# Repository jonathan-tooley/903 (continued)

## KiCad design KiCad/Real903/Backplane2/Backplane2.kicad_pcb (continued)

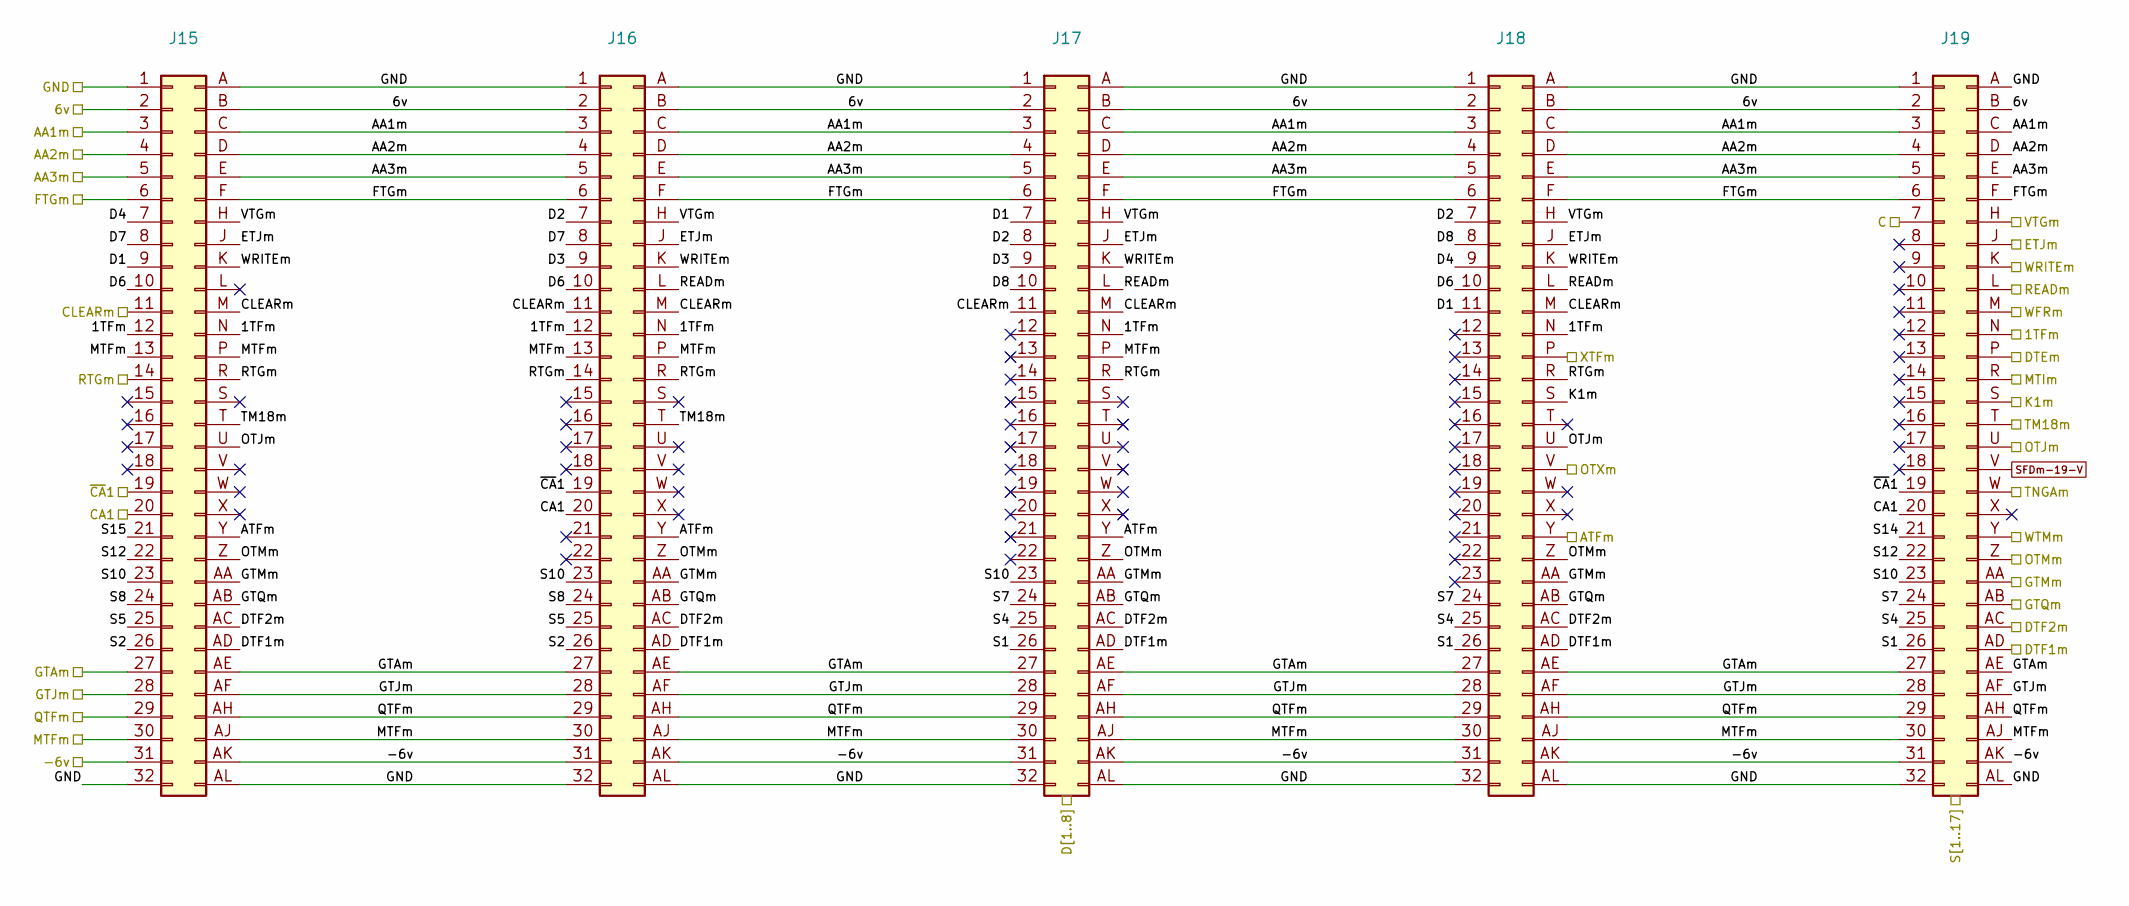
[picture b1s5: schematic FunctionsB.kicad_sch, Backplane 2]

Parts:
J15, J16, J17, J18, J19: DIN41612_B_2x32_Vertical

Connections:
0v: J15.1, J15.32, J15.A, J15.AL, J16.1, J16.32, J16.A, J16.AL, J17.1, J17.32, J17.A, J17.AL, J18.1, J18.32, J18.A, J18.AL, J19.1, J19.32, J19.A, J19.AL; also elsewhere on the board
6v: J15.2, J15.B, J16.2, J16.B, J17.2, J17.B, J18.2, J18.B, J19.2, J19.B; also elsewhere on the board
/DRIVERS/C: J19.7; also elsewhere on the board
/DRIVERS/DTEm: J19.P; also elsewhere on the board
/DRIVERS/MTFm: J15.13, J15.30, J15.AJ, J15.P, J16.13, J16.30, J16.AJ, J16.P, J17.30, J17.AJ, J17.P, J18.30, J18.AJ, J19.30, J19.AJ; also elsewhere on the board
/DRIVERS/MTIm: J19.R; also elsewhere on the board
/DRIVERS/TNGAm: J19.W; also elsewhere on the board
/DRIVERS/WFRm: J19.M; also elsewhere on the board
/DRIVERS/WTMm: J19.Y; also elsewhere on the board
/FunctionsA/1TFm: J15.12, J15.N, J16.12, J16.N, J17.N, J18.N, J19.N; also elsewhere on the board
/FunctionsA/AA1m: J15.3, J15.C, J16.3, J16.C, J17.3, J17.C, J18.3, J18.C, J19.3, J19.C; also elsewhere on the board
/FunctionsA/AA2m: J15.4, J15.D, J16.4, J16.D, J17.4, J17.D, J18.4, J18.D, J19.4, J19.D; also elsewhere on the board
/FunctionsA/AA3m: J15.5, J15.E, J16.5, J16.E, J17.5, J17.E, J18.5, J18.E, J19.5, J19.E; also elsewhere on the board
/FunctionsA/ATFm: J15.Y, J16.Y, J17.Y, J18.Y; also elsewhere on the board
/FunctionsA/D1: J15.9, J17.7, J18.11; also elsewhere on the board
/FunctionsA/D2: J16.7, J17.8, J18.7; also elsewhere on the board
/FunctionsA/D3: J16.9, J17.9; also elsewhere on the board
/FunctionsA/D4: J15.7, J18.9; also elsewhere on the board
/FunctionsA/D6: J15.10, J16.10, J18.10; also elsewhere on the board
/FunctionsA/D7: J15.8, J16.8; also elsewhere on the board
/FunctionsA/D8: J17.10, J18.8; also elsewhere on the board
/FunctionsA/FTGm: J15.6, J15.F, J16.6, J16.F, J17.6, J17.F, J18.6, J18.F, J19.6, J19.F; also elsewhere on the board
/FunctionsA/GTAm: J15.27, J15.AE, J16.27, J16.AE, J17.27, J17.AE, J18.27, J18.AE, J19.27, J19.AE; also elsewhere on the board
/FunctionsA/GTJm: J15.28, J15.AF, J16.28, J16.AF, J17.28, J17.AF, J18.28, J18.AF, J19.28, J19.AF; also elsewhere on the board
/FunctionsA/GTQm: J15.AB, J16.AB, J17.AB, J18.AB, J19.AB; also elsewhere on the board
/FunctionsA/OTJm: J15.U, J18.U, J19.U; also elsewhere on the board
/FunctionsA/OTMm: J15.Z, J16.Z, J17.Z, J18.Z, J19.Z; also elsewhere on the board
/FunctionsA/OTXm: J18.V; also elsewhere on the board
/FunctionsA/READm: J16.L, J17.L, J18.L, J19.L; also elsewhere on the board
/FunctionsA/RTGm: J15.14, J15.R, J16.14, J16.R, J17.R, J18.R; also elsewhere on the board
/FunctionsA/S1: J17.26, J18.26, J19.26; also elsewhere on the board
/FunctionsA/S2: J15.26, J16.26; also elsewhere on the board
/FunctionsA/S4: J17.25, J18.25, J19.25; also elsewhere on the board
/FunctionsA/S5: J15.25, J16.25; also elsewhere on the board
/FunctionsA/S7: J17.24, J18.24, J19.24; also elsewhere on the board
/FunctionsA/S8: J15.24, J16.24; also elsewhere on the board
/FunctionsA/S10: J15.23, J16.23, J17.23, J19.23; also elsewhere on the board
/FunctionsA/S12: J15.22, J19.22; also elsewhere on the board
/FunctionsA/S14: J19.21; also elsewhere on the board
/FunctionsA/S15: J15.21; also elsewhere on the board
/FunctionsA/WRITEm: J15.K, J16.K, J17.K, J18.K, J19.K; also elsewhere on the board
/FunctionsA/XTFm: J18.P; also elsewhere on the board
/FunctionsB/CA1: J15.20, J16.20, J19.20; also elsewhere on the board
/FunctionsB/CLEARm: J15.11, J15.M, J16.11, J16.M, J17.11, J17.M, J18.M; also elsewhere on the board
/FunctionsB/DTF1m: J15.AD, J16.AD, J17.AD, J18.AD, J19.AD; also elsewhere on the board
/FunctionsB/DTF2m: J15.AC, J16.AC, J17.AC, J18.AC, J19.AC; also elsewhere on the board
/FunctionsB/ETJm: J15.J, J16.J, J17.J, J18.J, J19.J; also elsewhere on the board
/FunctionsB/GTMm: J15.AA, J16.AA, J17.AA, J18.AA, J19.AA; also elsewhere on the board
/FunctionsB/K1m: J18.S, J19.S; also elsewhere on the board
/FunctionsB/QTFm: J15.29, J15.AH, J16.29, J16.AH, J17.29, J17.AH, J18.29, J18.AH, J19.29, J19.AH; also elsewhere on the board
/FunctionsB/TM18m: J15.T, J16.T, J19.T; also elsewhere on the board
/FunctionsB/VTGm: J15.H, J16.H, J17.H, J18.H, J19.H; also elsewhere on the board
/FunctionsB/~CA1: J15.19, J16.19, J19.19; also elsewhere on the board
Neg6v: J15.31, J15.AK, J16.31, J16.AK, J17.31, J17.AK, J18.31, J18.AK, J19.31, J19.AK; also elsewhere on the board
SFDm-19-V: J19.V; also elsewhere on the board

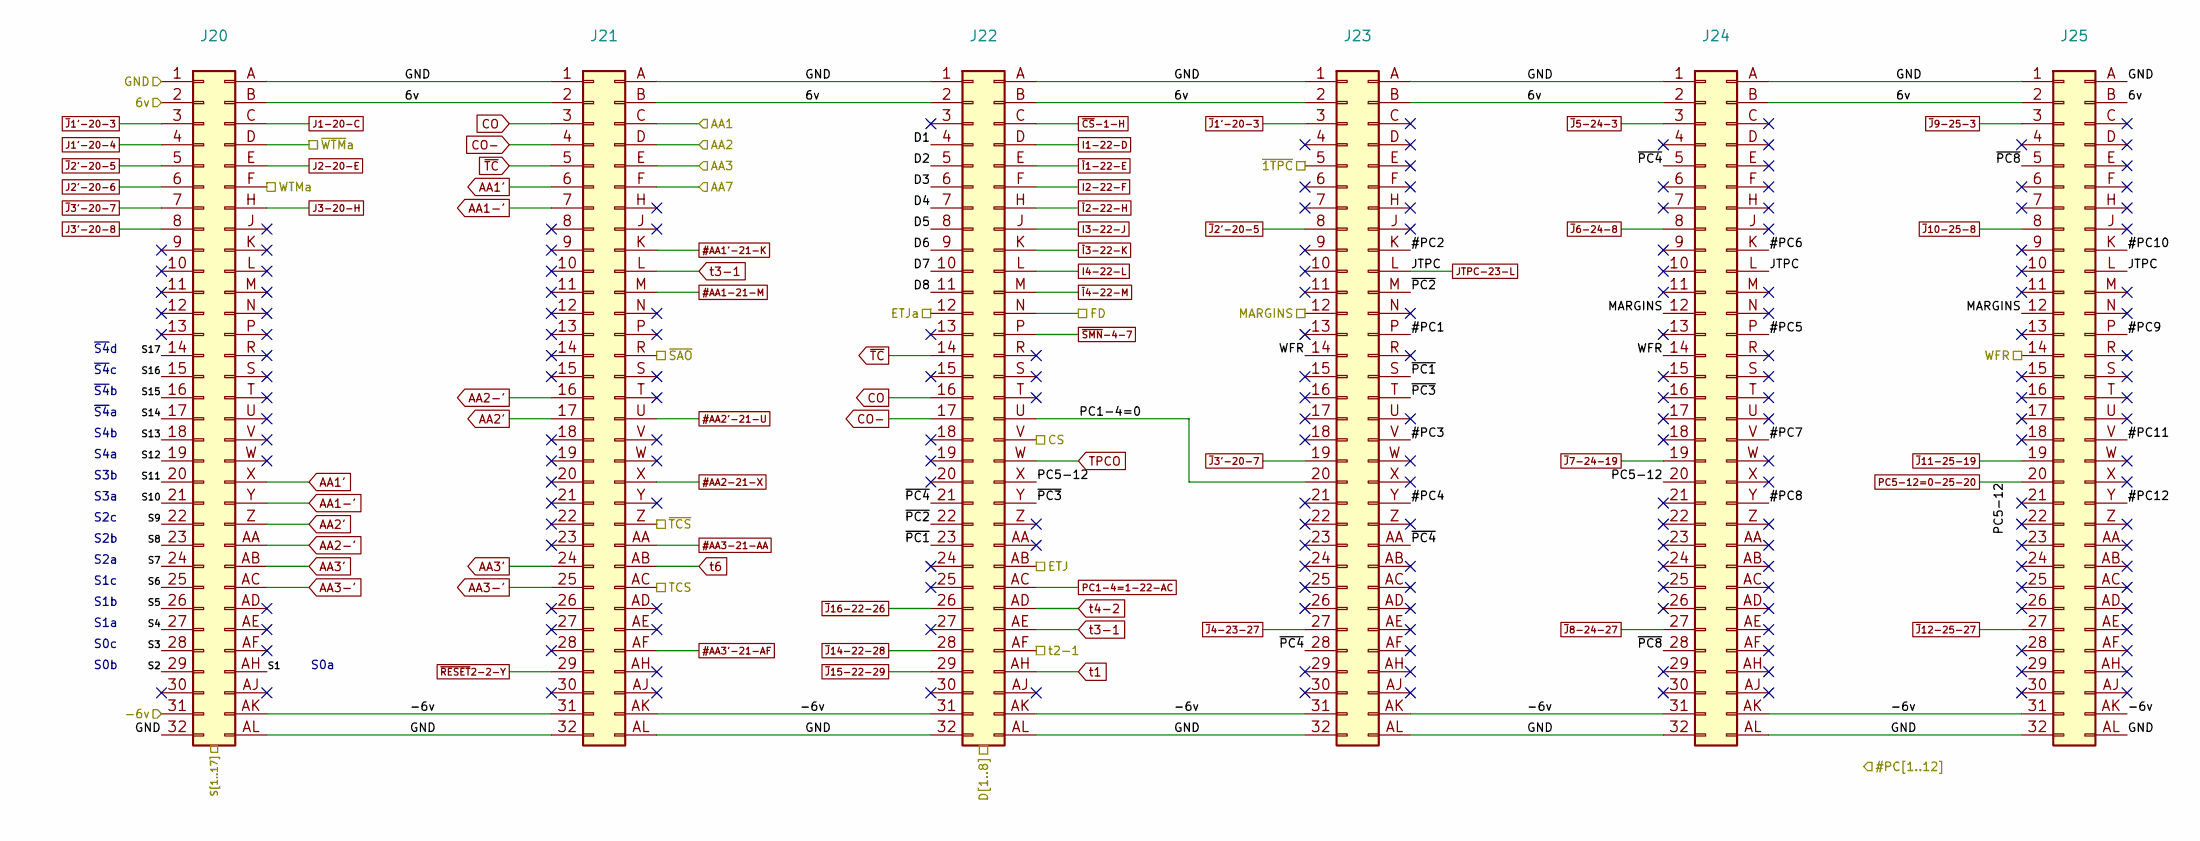
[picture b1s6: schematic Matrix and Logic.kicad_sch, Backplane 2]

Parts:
J20, J21, J22, J23, J24, J25: DIN41612_B_2x32_Vertical

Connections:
0v: J20.1, J20.32, J20.A, J20.AL, J21.1, J21.32, J21.A, J21.AL, J22.1, J22.32, J22.A, J22.AL, J23.1, J23.32, J23.A, J23.AL, J24.1, J24.32, J24.A, J24.AL, J25.1, J25.32, J25.A, J25.AL; also elsewhere on the board
6v: J20.2, J20.B, J21.2, J21.B, J22.2, J22.B, J23.2, J23.B, J24.2, J24.B, J25.2, J25.B; also elsewhere on the board
#AA1'-21-K: J21.K; also elsewhere on the board
#AA1-21-M: J21.M; also elsewhere on the board
#AA2'-21-U: J21.U; also elsewhere on the board
#AA2-21-X: J21.X; also elsewhere on the board
#AA3'-21-AF: J21.AF; also elsewhere on the board
#AA3-21-AA: J21.AA; also elsewhere on the board
/Connections/#PC1: J23.P; also elsewhere on the board
/Connections/#PC2: J23.K; also elsewhere on the board
/Connections/#PC3: J23.V; also elsewhere on the board
/Connections/#PC4: J23.Y; also elsewhere on the board
/Connections/#PC5: J24.P; also elsewhere on the board
/Connections/#PC6: J24.K; also elsewhere on the board
/Connections/#PC7: J24.V; also elsewhere on the board
/Connections/#PC8: J24.Y; also elsewhere on the board
/Connections/#PC9: J25.P; also elsewhere on the board
/Connections/#PC10: J25.K; also elsewhere on the board
/Connections/#PC11: J25.V; also elsewhere on the board
/Connections/#PC12: J25.Y; also elsewhere on the board
/DRIVERS/AA7: J21.F; also elsewhere on the board
/DRIVERS/ETJ: J22.AB; also elsewhere on the board
/DRIVERS/ETJa: J22.12; also elsewhere on the board
/DRIVERS/FD: J22.N; also elsewhere on the board
/DRIVERS/TCS: J21.AC; also elsewhere on the board
/DRIVERS/t2-1: J22.AF; also elsewhere on the board
/DRIVERS/~TCS: J21.Z; also elsewhere on the board
/FunctionsA/AA1m: J21.C; also elsewhere on the board
/FunctionsA/AA2m: J21.D; also elsewhere on the board
/FunctionsA/AA3m: J21.E; also elsewhere on the board
/FunctionsA/D1: J22.4; also elsewhere on the board
/FunctionsA/D2: J22.5; also elsewhere on the board
/FunctionsA/D3: J22.6; also elsewhere on the board
/FunctionsA/D4: J22.7; also elsewhere on the board
/FunctionsA/D5: J22.8; also elsewhere on the board
/FunctionsA/D6: J22.9; also elsewhere on the board
/FunctionsA/D7: J22.10; also elsewhere on the board
/FunctionsA/D8: J22.11; also elsewhere on the board
/FunctionsA/S1: J20.AH; also elsewhere on the board
/FunctionsA/S2: J20.29; also elsewhere on the board
/FunctionsA/S3: J20.28; also elsewhere on the board
/FunctionsA/S4: J20.27; also elsewhere on the board
/FunctionsA/S5: J20.26; also elsewhere on the board
/FunctionsA/S6: J20.25; also elsewhere on the board
/FunctionsA/S7: J20.24; also elsewhere on the board
/FunctionsA/S8: J20.23; also elsewhere on the board
/FunctionsA/S9: J20.22; also elsewhere on the board
/FunctionsA/S10: J20.21; also elsewhere on the board
/FunctionsA/S11: J20.20; also elsewhere on the board
/FunctionsA/S12: J20.19; also elsewhere on the board
/FunctionsA/S13: J20.18; also elsewhere on the board
/FunctionsA/S14: J20.17; also elsewhere on the board
/FunctionsA/S15: J20.16; also elsewhere on the board
/FunctionsA/S16: J20.15; also elsewhere on the board
/FunctionsA/S17: J20.14; also elsewhere on the board
/Matrix and Logic/MARGINS: J23.12, J24.12, J25.12; also elsewhere on the board
/Matrix and Logic/PC1-4=0: J22.U, J23.20
/Matrix and Logic/WFR: J23.14, J24.14, J25.14; also elsewhere on the board
/Matrix and Logic/~1TPC: J23.5; also elsewhere on the board
/Matrix and Logic/~PC1: J22.23, J23.S
/Matrix and Logic/~PC2: J22.22, J23.M
/Matrix and Logic/~PC3: J22.Y, J23.T
/Matrix and Logic/~PC4: J22.21, J23.28, J23.AA, J24.5
/Matrix and Logic/~PC8: J24.28, J25.5
/Matrix and Logic/~WTMa: J20.D; also elsewhere on the board
/TIMING/CS: J22.V; also elsewhere on the board
/TIMING/~SAO: J21.R; also elsewhere on the board
AA1': J20.X, J21.6
AA1-': J20.Y, J21.7
AA2': J20.Z, J21.17
AA2-': J20.AA, J21.16
AA3': J20.AB, J21.24
AA3-': J20.AC, J21.25
CO: J21.3, J22.16
CO-: J21.4, J22.17
I1-22-D: J22.D; also elsewhere on the board
I2-22-F: J22.F; also elsewhere on the board
I3-22-J: J22.J; also elsewhere on the board
I4-22-L: J22.L; also elsewhere on the board
J1'-20-4: J20.4; also elsewhere on the board
J1-20-C: J20.C; also elsewhere on the board
J2'-20-6: J20.6; also elsewhere on the board
J2-20-E: J20.E; also elsewhere on the board
J3'-20-8: J20.8; also elsewhere on the board
J3-20-H: J20.H; also elsewhere on the board
JTPC-23-L: J23.L, J24.L, J25.L; also elsewhere on the board
Neg6v: J20.31, J20.AK, J21.31, J21.AK, J22.31, J22.AK, J23.31, J23.AK, J24.31, J24.AK, J25.31, J25.AK; also elsewhere on the board
PC1-4=1-22-AC: J22.AC; also elsewhere on the board
PC5-12=0-25-20: J22.X, J24.20, J25.20; also elsewhere on the board
TPCO: J22.W; also elsewhere on the board
WTMa-8-21: J20.F; also elsewhere on the board
t1: J22.AH; also elsewhere on the board
t3-1: J21.L, J22.AE
t4-2: J22.AD; also elsewhere on the board
t6: J21.AB; also elsewhere on the board
~CS-1-H: J22.C; also elsewhere on the board
~I1-22-E: J22.E; also elsewhere on the board
~I2-22-H: J22.H; also elsewhere on the board
~I3-22-K: J22.K; also elsewhere on the board
~I4-22-M: J22.M; also elsewhere on the board
~J1'-20-3: J20.3, J23.3; also elsewhere on the board
~J2'-20-5: J20.5, J23.8; also elsewhere on the board
~J3'-20-7: J20.7, J23.19; also elsewhere on the board
~J4-23-27: J23.27; also elsewhere on the board
~J5-24-3: J24.3; also elsewhere on the board
~J6-24-8: J24.8; also elsewhere on the board
~J7-24-19: J24.19; also elsewhere on the board
~J8-24-27: J24.27; also elsewhere on the board
~J9-25-3: J25.3; also elsewhere on the board
~J10-25-8: J25.8; also elsewhere on the board
~J11-25-19: J25.19; also elsewhere on the board
~J12-25-27: J25.27; also elsewhere on the board
~J14-22-28: J22.28; also elsewhere on the board
~J15-22-29: J22.29; also elsewhere on the board
~J16-22-26: J22.26; also elsewhere on the board
~RESET2-2-Y: J21.29; also elsewhere on the board
~SMN-4-7: J22.P; also elsewhere on the board
~TC: J21.5, J22.14

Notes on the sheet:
S1b
S2a
~{S4}b
S0c
S3b
~{S4}a
S2b
~{S4}c
S4b
~{S4}d
S0a
S4a
S1a
S2c
S1c
S0b
S3a

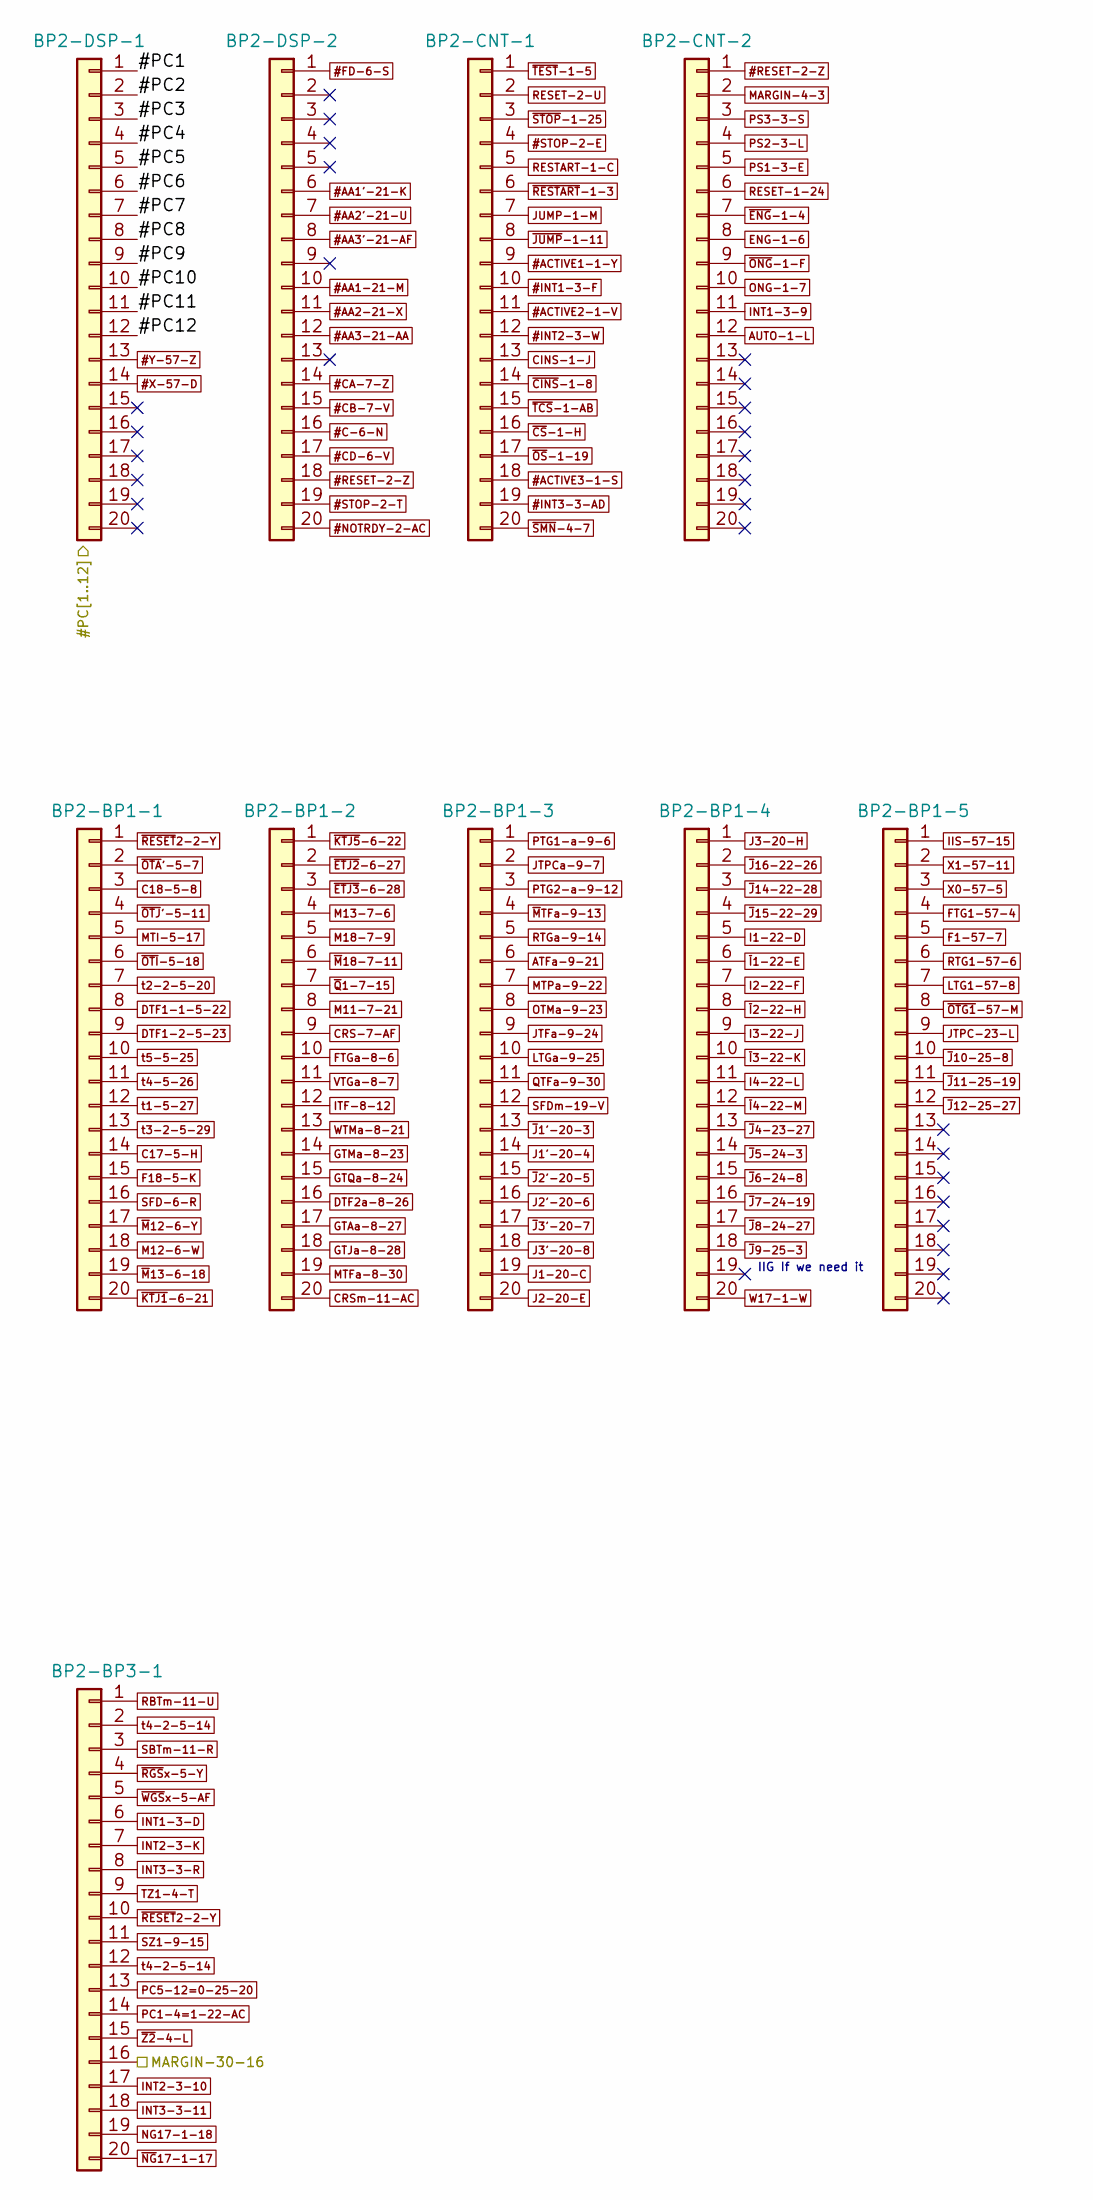
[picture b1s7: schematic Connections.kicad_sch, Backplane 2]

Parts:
BP2-BP1-1, BP2-BP1-2, BP2-BP1-3, BP2-BP1-4, BP2-BP1-5, BP2-BP3-1, BP2-CNT-1, BP2-CNT-2, BP2-DSP-1, BP2-DSP-2: IDC-Header_2x10_P2.54mm_Latch_Vertical

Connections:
#AA1'-21-K: BP2-DSP-2.6; also elsewhere on the board
#AA1-21-M: BP2-DSP-2.10; also elsewhere on the board
#AA2'-21-U: BP2-DSP-2.7; also elsewhere on the board
#AA2-21-X: BP2-DSP-2.11; also elsewhere on the board
#AA3'-21-AF: BP2-DSP-2.8; also elsewhere on the board
#AA3-21-AA: BP2-DSP-2.12; also elsewhere on the board
#ACTIVE1-1-Y: BP2-CNT-1.9; also elsewhere on the board
#ACTIVE2-1-V: BP2-CNT-1.11; also elsewhere on the board
#ACTIVE3-1-S: BP2-CNT-1.18; also elsewhere on the board
#C-6-N: BP2-DSP-2.16; also elsewhere on the board
#CA-7-Z: BP2-DSP-2.14; also elsewhere on the board
#CB-7-V: BP2-DSP-2.15; also elsewhere on the board
#CD-6-V: BP2-DSP-2.17; also elsewhere on the board
#FD-6-S: BP2-DSP-2.1; also elsewhere on the board
#INT1-3-F: BP2-CNT-1.10; also elsewhere on the board
#INT2-3-W: BP2-CNT-1.12; also elsewhere on the board
#INT3-3-AD: BP2-CNT-1.19; also elsewhere on the board
#NOTRDY-2-AC: BP2-DSP-2.20; also elsewhere on the board
#RESET-2-Z: BP2-CNT-2.1, BP2-DSP-2.18; also elsewhere on the board
#STOP-2-E: BP2-CNT-1.4; also elsewhere on the board
#STOP-2-T: BP2-DSP-2.19; also elsewhere on the board
#X-57-D: BP2-DSP-1.14; also elsewhere on the board
#Y-57-Z: BP2-DSP-1.13; also elsewhere on the board
/Connections/#PC1: BP2-DSP-1.1; also elsewhere on the board
/Connections/#PC2: BP2-DSP-1.2; also elsewhere on the board
/Connections/#PC3: BP2-DSP-1.3; also elsewhere on the board
/Connections/#PC4: BP2-DSP-1.4; also elsewhere on the board
/Connections/#PC5: BP2-DSP-1.5; also elsewhere on the board
/Connections/#PC6: BP2-DSP-1.6; also elsewhere on the board
/Connections/#PC7: BP2-DSP-1.7; also elsewhere on the board
/Connections/#PC8: BP2-DSP-1.8; also elsewhere on the board
/Connections/#PC9: BP2-DSP-1.9; also elsewhere on the board
/Connections/#PC10: BP2-DSP-1.10; also elsewhere on the board
/Connections/#PC11: BP2-DSP-1.11; also elsewhere on the board
/Connections/#PC12: BP2-DSP-1.12; also elsewhere on the board
/Matrix and Logic/MARGINS: BP2-BP3-1.16; also elsewhere on the board
ATFa-9-21: BP2-BP1-3.6; also elsewhere on the board
AUTO-1-L: BP2-CNT-2.12; also elsewhere on the board
C17-5-H: BP2-BP1-1.14; also elsewhere on the board
C18-5-8: BP2-BP1-1.3; also elsewhere on the board
CINS-1-J: BP2-CNT-1.13; also elsewhere on the board
CRS-7-AF: BP2-BP1-2.9; also elsewhere on the board
CRSm-11-AC: BP2-BP1-2.20; also elsewhere on the board
DTF1-1-5-22: BP2-BP1-1.8; also elsewhere on the board
DTF1-2-5-23: BP2-BP1-1.9; also elsewhere on the board
DTF2a-8-26: BP2-BP1-2.16; also elsewhere on the board
ENG-1-6: BP2-CNT-2.8; also elsewhere on the board
F1-57-7: BP2-BP1-5.5; also elsewhere on the board
F18-5-K: BP2-BP1-1.15; also elsewhere on the board
FTG1-57-4: BP2-BP1-5.4; also elsewhere on the board
FTGa-8-6: BP2-BP1-2.10; also elsewhere on the board
GTAa-8-27: BP2-BP1-2.17; also elsewhere on the board
GTJa-8-28: BP2-BP1-2.18; also elsewhere on the board
GTMa-8-23: BP2-BP1-2.14; also elsewhere on the board
GTQa-8-24: BP2-BP1-2.15; also elsewhere on the board
I1-22-D: BP2-BP1-4.5; also elsewhere on the board
I2-22-F: BP2-BP1-4.7; also elsewhere on the board
I3-22-J: BP2-BP1-4.9; also elsewhere on the board
I4-22-L: BP2-BP1-4.11; also elsewhere on the board
IIS-57-15: BP2-BP1-5.1; also elsewhere on the board
INT1-3-9: BP2-CNT-2.11; also elsewhere on the board
INT1-3-D: BP2-BP3-1.6; also elsewhere on the board
INT2-3-10: BP2-BP3-1.17; also elsewhere on the board
INT2-3-K: BP2-BP3-1.7; also elsewhere on the board
INT3-3-11: BP2-BP3-1.18; also elsewhere on the board
INT3-3-R: BP2-BP3-1.8; also elsewhere on the board
ITF-8-12: BP2-BP1-2.12; also elsewhere on the board
J1'-20-4: BP2-BP1-3.14; also elsewhere on the board
J1-20-C: BP2-BP1-3.19; also elsewhere on the board
J2'-20-6: BP2-BP1-3.16; also elsewhere on the board
J2-20-E: BP2-BP1-3.20; also elsewhere on the board
J3'-20-8: BP2-BP1-3.18; also elsewhere on the board
J3-20-H: BP2-BP1-4.1; also elsewhere on the board
JTFa-9-24: BP2-BP1-3.9; also elsewhere on the board
JTPC-23-L: BP2-BP1-5.9; also elsewhere on the board
JTPCa-9-7: BP2-BP1-3.2; also elsewhere on the board
JUMP-1-M: BP2-CNT-1.7; also elsewhere on the board
LTG1-57-8: BP2-BP1-5.7; also elsewhere on the board
LTGa-9-25: BP2-BP1-3.10; also elsewhere on the board
M11-7-21: BP2-BP1-2.8; also elsewhere on the board
M12-6-W: BP2-BP1-1.18; also elsewhere on the board
M13-7-6: BP2-BP1-2.4; also elsewhere on the board
M18-7-9: BP2-BP1-2.5; also elsewhere on the board
MARGIN-4-3: BP2-CNT-2.2; also elsewhere on the board
MTFa-8-30: BP2-BP1-2.19; also elsewhere on the board
MTI-5-17: BP2-BP1-1.5; also elsewhere on the board
MTPa-9-22: BP2-BP1-3.7; also elsewhere on the board
NG17-1-18: BP2-BP3-1.19; also elsewhere on the board
ONG-1-7: BP2-CNT-2.10; also elsewhere on the board
OTMa-9-23: BP2-BP1-3.8; also elsewhere on the board
PC1-4=1-22-AC: BP2-BP3-1.14; also elsewhere on the board
PC5-12=0-25-20: BP2-BP3-1.13; also elsewhere on the board
PS1-3-E: BP2-CNT-2.5; also elsewhere on the board
PS2-3-L: BP2-CNT-2.4; also elsewhere on the board
PS3-3-S: BP2-CNT-2.3; also elsewhere on the board
PTG1-a-9-6: BP2-BP1-3.1; also elsewhere on the board
PTG2-a-9-12: BP2-BP1-3.3; also elsewhere on the board
QTFa-9-30: BP2-BP1-3.11; also elsewhere on the board
RBTm-11-U: BP2-BP3-1.1; also elsewhere on the board
RESET-1-24: BP2-CNT-2.6; also elsewhere on the board
RESET-2-U: BP2-CNT-1.2; also elsewhere on the board
RESTART-1-C: BP2-CNT-1.5; also elsewhere on the board
RTG1-57-6: BP2-BP1-5.6; also elsewhere on the board
RTGa-9-14: BP2-BP1-3.5; also elsewhere on the board
SBTm-11-R: BP2-BP3-1.3; also elsewhere on the board
SFD-6-R: BP2-BP1-1.16; also elsewhere on the board
SFDm-19-V: BP2-BP1-3.12; also elsewhere on the board
SZ1-9-15: BP2-BP3-1.11; also elsewhere on the board
TZ1-4-T: BP2-BP3-1.9; also elsewhere on the board
VTGa-8-7: BP2-BP1-2.11; also elsewhere on the board
W17-1-W: BP2-BP1-4.20; also elsewhere on the board
WTMa-8-21: BP2-BP1-2.13; also elsewhere on the board
X0-57-5: BP2-BP1-5.3; also elsewhere on the board
X1-57-11: BP2-BP1-5.2; also elsewhere on the board
t1-5-27: BP2-BP1-1.12; also elsewhere on the board
t2-2-5-20: BP2-BP1-1.7; also elsewhere on the board
t3-2-5-29: BP2-BP1-1.13; also elsewhere on the board
t4-2-5-14: BP2-BP3-1.2, BP2-BP3-1.12; also elsewhere on the board
t4-5-26: BP2-BP1-1.11; also elsewhere on the board
t5-5-25: BP2-BP1-1.10; also elsewhere on the board
~CINS-1-8: BP2-CNT-1.14; also elsewhere on the board
~CS-1-H: BP2-CNT-1.16; also elsewhere on the board
~ENG-1-4: BP2-CNT-2.7; also elsewhere on the board
~ETJ2-6-27: BP2-BP1-2.2; also elsewhere on the board
~ETJ3-6-28: BP2-BP1-2.3; also elsewhere on the board
~I1-22-E: BP2-BP1-4.6; also elsewhere on the board
~I2-22-H: BP2-BP1-4.8; also elsewhere on the board
~I3-22-K: BP2-BP1-4.10; also elsewhere on the board
~I4-22-M: BP2-BP1-4.12; also elsewhere on the board
~JUMP-1-11: BP2-CNT-1.8; also elsewhere on the board
~J1'-20-3: BP2-BP1-3.13; also elsewhere on the board
~J2'-20-5: BP2-BP1-3.15; also elsewhere on the board
~J3'-20-7: BP2-BP1-3.17; also elsewhere on the board
~J4-23-27: BP2-BP1-4.13; also elsewhere on the board
~J5-24-3: BP2-BP1-4.14; also elsewhere on the board
~J6-24-8: BP2-BP1-4.15; also elsewhere on the board
~J7-24-19: BP2-BP1-4.16; also elsewhere on the board
~J8-24-27: BP2-BP1-4.17; also elsewhere on the board
~J9-25-3: BP2-BP1-4.18; also elsewhere on the board
~J10-25-8: BP2-BP1-5.10; also elsewhere on the board
~J11-25-19: BP2-BP1-5.11; also elsewhere on the board
~J12-25-27: BP2-BP1-5.12; also elsewhere on the board
~J14-22-28: BP2-BP1-4.3; also elsewhere on the board
~J15-22-29: BP2-BP1-4.4; also elsewhere on the board
~J16-22-26: BP2-BP1-4.2; also elsewhere on the board
~KTJ1-6-21: BP2-BP1-1.20; also elsewhere on the board
~KTJ5-6-22: BP2-BP1-2.1; also elsewhere on the board
~M12-6-Y: BP2-BP1-1.17; also elsewhere on the board
~M13-6-18: BP2-BP1-1.19; also elsewhere on the board
~M18-7-11: BP2-BP1-2.6; also elsewhere on the board
~MTFa-9-13: BP2-BP1-3.4; also elsewhere on the board
~NG17-1-17: BP2-BP3-1.20; also elsewhere on the board
~ONG-1-F: BP2-CNT-2.9; also elsewhere on the board
~OS-1-19: BP2-CNT-1.17; also elsewhere on the board
~OTA'-5-7: BP2-BP1-1.2; also elsewhere on the board
~OTG1-57-M: BP2-BP1-5.8; also elsewhere on the board
~OTI-5-18: BP2-BP1-1.6; also elsewhere on the board
~OTJ'-5-11: BP2-BP1-1.4; also elsewhere on the board
~Q1-7-15: BP2-BP1-2.7; also elsewhere on the board
~RESET2-2-Y: BP2-BP1-1.1, BP2-BP3-1.10; also elsewhere on the board
~RESTART-1-3: BP2-CNT-1.6; also elsewhere on the board
~RGSx-5-Y: BP2-BP3-1.4; also elsewhere on the board
~SMN-4-7: BP2-CNT-1.20; also elsewhere on the board
~STOP-1-25: BP2-CNT-1.3; also elsewhere on the board
~TCS-1-AB: BP2-CNT-1.15; also elsewhere on the board
~TEST-1-5: BP2-CNT-1.1; also elsewhere on the board
~WGSx-5-AF: BP2-BP3-1.5; also elsewhere on the board
~Z2-4-L: BP2-BP3-1.15; also elsewhere on the board

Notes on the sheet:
IIG If we need it

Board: 2 copper layers, 39 parts (26 on the bottom side), 363 nets, no tracks yet.

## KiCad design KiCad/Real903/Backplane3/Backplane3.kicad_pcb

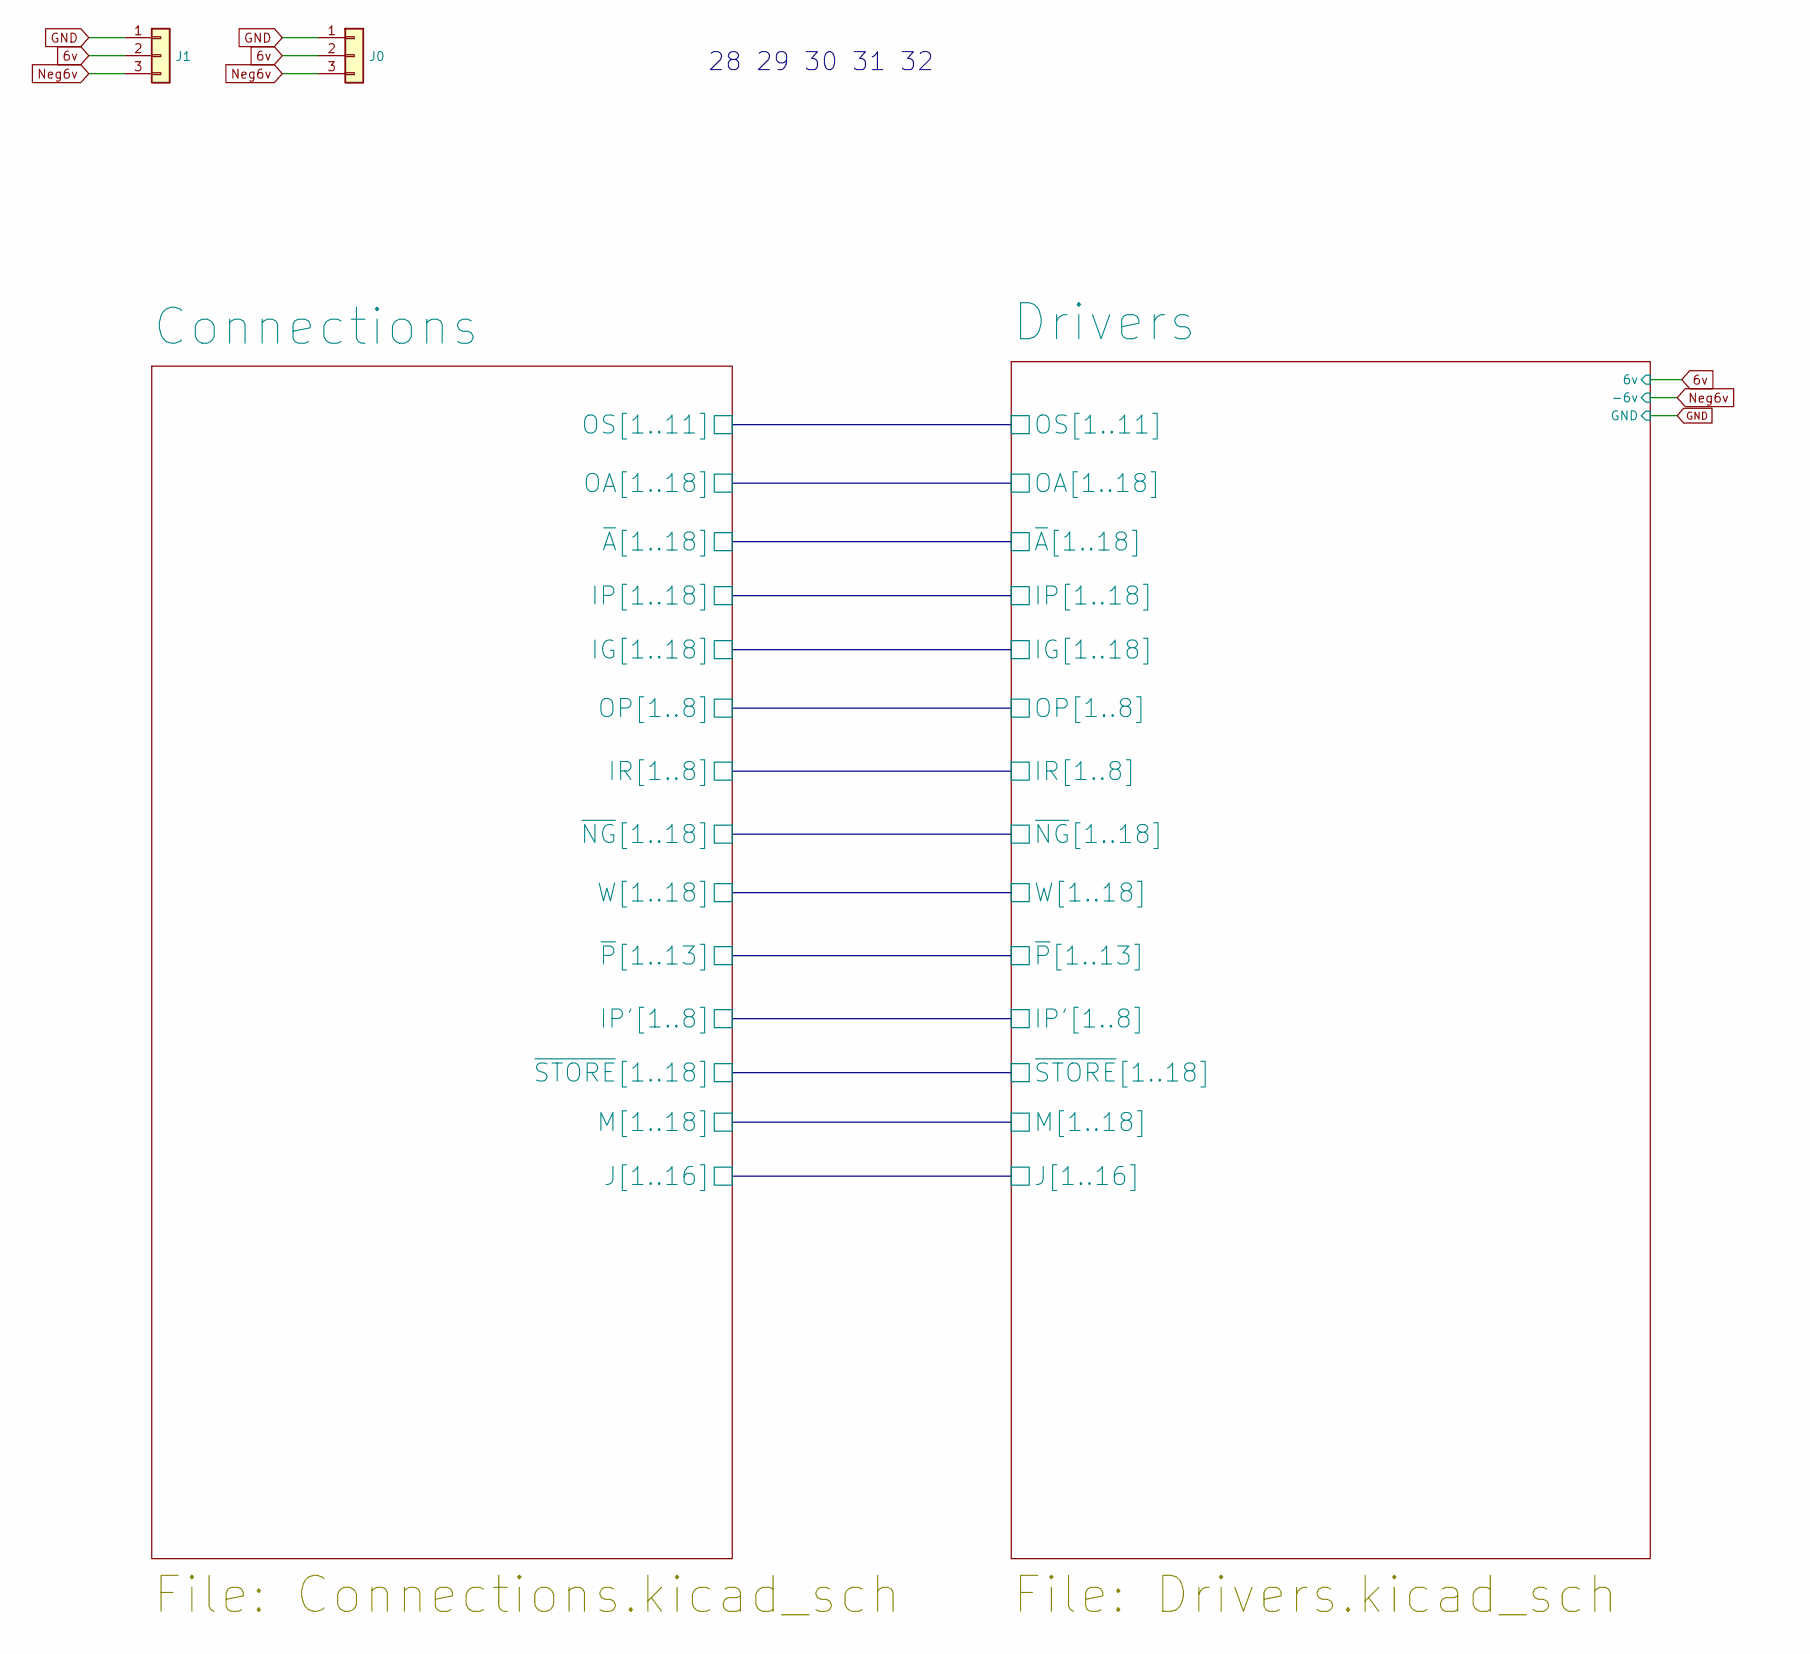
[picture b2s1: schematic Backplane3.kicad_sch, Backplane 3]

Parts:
J0, J1: TerminalBlock_5.08_1x03

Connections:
6v: J0.2, J1.2; also elsewhere on the board
GND: J0.1, J1.1; also elsewhere on the board
Neg6v: J0.3, J1.3; also elsewhere on the board

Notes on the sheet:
28 29 30 31 32
